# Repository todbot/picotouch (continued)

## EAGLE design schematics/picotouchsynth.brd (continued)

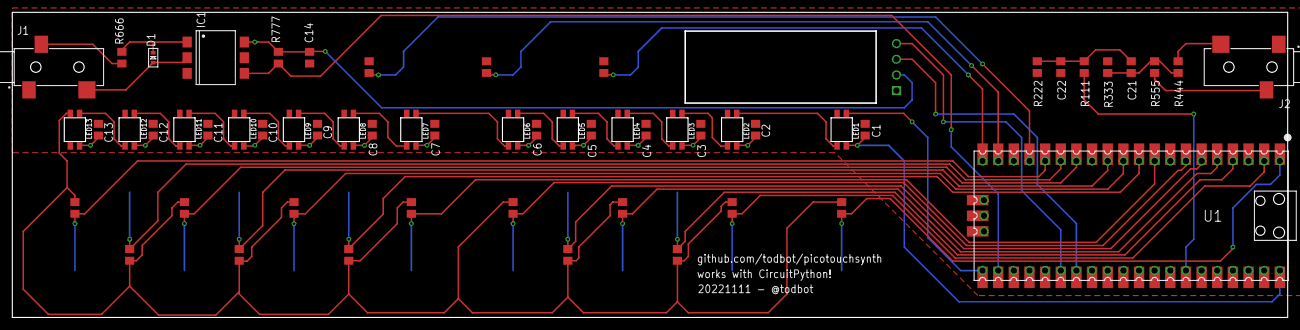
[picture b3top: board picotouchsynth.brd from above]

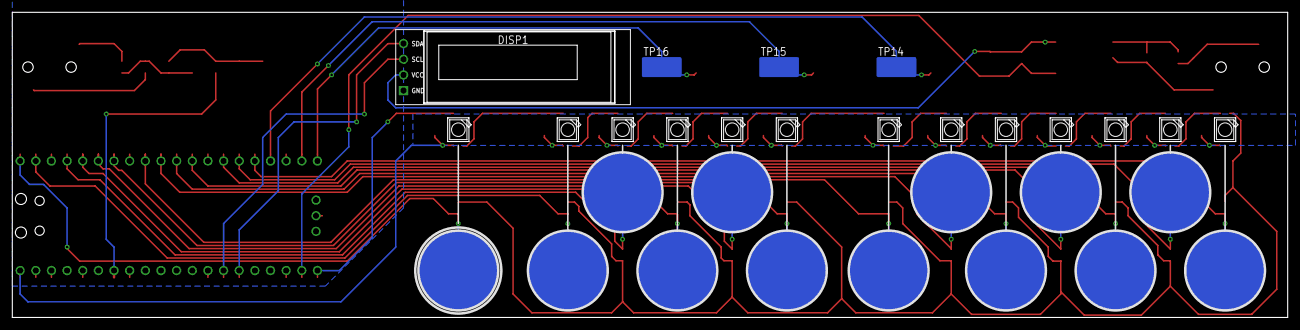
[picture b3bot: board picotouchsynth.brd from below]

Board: 2 copper layers, 207.0 x 49.5 mm, 74 parts (30 on the bottom side), 45 nets.

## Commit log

2021-04-13 first
2021-04-14 submitted to pcbway
2021-04-14 added silkshot
2021-04-14 readme
2021-04-14 start on the firmware
2021-04-14 make bigger
2021-04-14 try out debouncer
2021-04-14 actually works!
2021-04-20 aha fix touch sensitivity of fingers hitting traces
2021-04-21 update instructions
2021-04-21 added enclosure design; added oshpark link
2021-04-21 added digikey cart
2021-04-22 first (bad) cut at ch/pitch/mod buttons
2022-11-19 maybe picotouchsynth
2022-11-19 more picotouchsynth
2022-11-23 picotouchsynth version sent to fab
2023-01-17 modbuttons circuitpython
2023-01-17 add simple arduino demo
2023-01-19 sent picotouch_smd to fab
2023-02-02 picotouch_code.py matches new silkscreen
2023-02-02 added picotouch_smd pic
2023-02-03 small typo
2023-02-03 add arduino midicontroller1 example, it mostly works.
2023-02-08 soldering video
2023-02-10 added adafruit_ticks ref, thx Kirby!
2023-02-11 note about copying over code.py. thx John!
2023-02-12 update circuitpython code
2023-02-12 small cirpy reorg
2023-02-12 woops need that for LED blinkin
2023-02-12 readme cleanup
2023-02-13 added picotouch macropad demo
2023-02-13 first commit of midislider
2023-02-14 midislider: forget release as 0 value, just do it easy like
2023-02-14 added links to midislider and macropad examples
2023-02-15 grid idea
2023-02-15 more grid idea
2023-02-15 grid idea has cutout now
2023-02-16 reorg grid idea
2023-02-18 do note off correctly for held notes and octave change. fixes #2
2023-02-21 picotouch_grid test code
2023-02-26 picotouch_grid: PIO capsense rows, midi controller works pretty well
2023-03-01 added gpio pins 16,17,18,19 as smd touchpads for hacking
2023-03-01 reorg and checkin example tests
2023-03-02 added test points
2023-03-06 demo using mozzi in w/ hacked picotouch
2023-03-07 more experiments with touchpads
2023-03-07 arduino: better touch library! uses higher drive strength to charge pads
2023-03-08 arduino: clean up touchytouch capsense library
2023-03-17 picotouch_gridD: usb and serial midi
2023-04-07 added but pico dual smd footprint is too wide
2023-06-18 add (bad) aftertouch example
2023-06-26 make more clear that tindie picotouch has resistors
2023-08-16 move confusing research code to research dir
2023-08-16 first picotouch_synth, (actually sixth but first of this style)
2023-08-16 first cut at picotouch_synth pcb art
2023-08-16 adding slidercase from printables
2023-08-16 almost final artwork
2023-08-16 moved picotouch_synth to its own repo
2023-08-16 test -> hwtest
2023-08-18 fix hwtest code
2023-10-09 add link to picotouch_synth
2023-11-27 add photo
2023-11-27 update press links
2024-03-22 circuitpython hwtest: fix up wow super old bug
2024-09-01 0.1 uf2
